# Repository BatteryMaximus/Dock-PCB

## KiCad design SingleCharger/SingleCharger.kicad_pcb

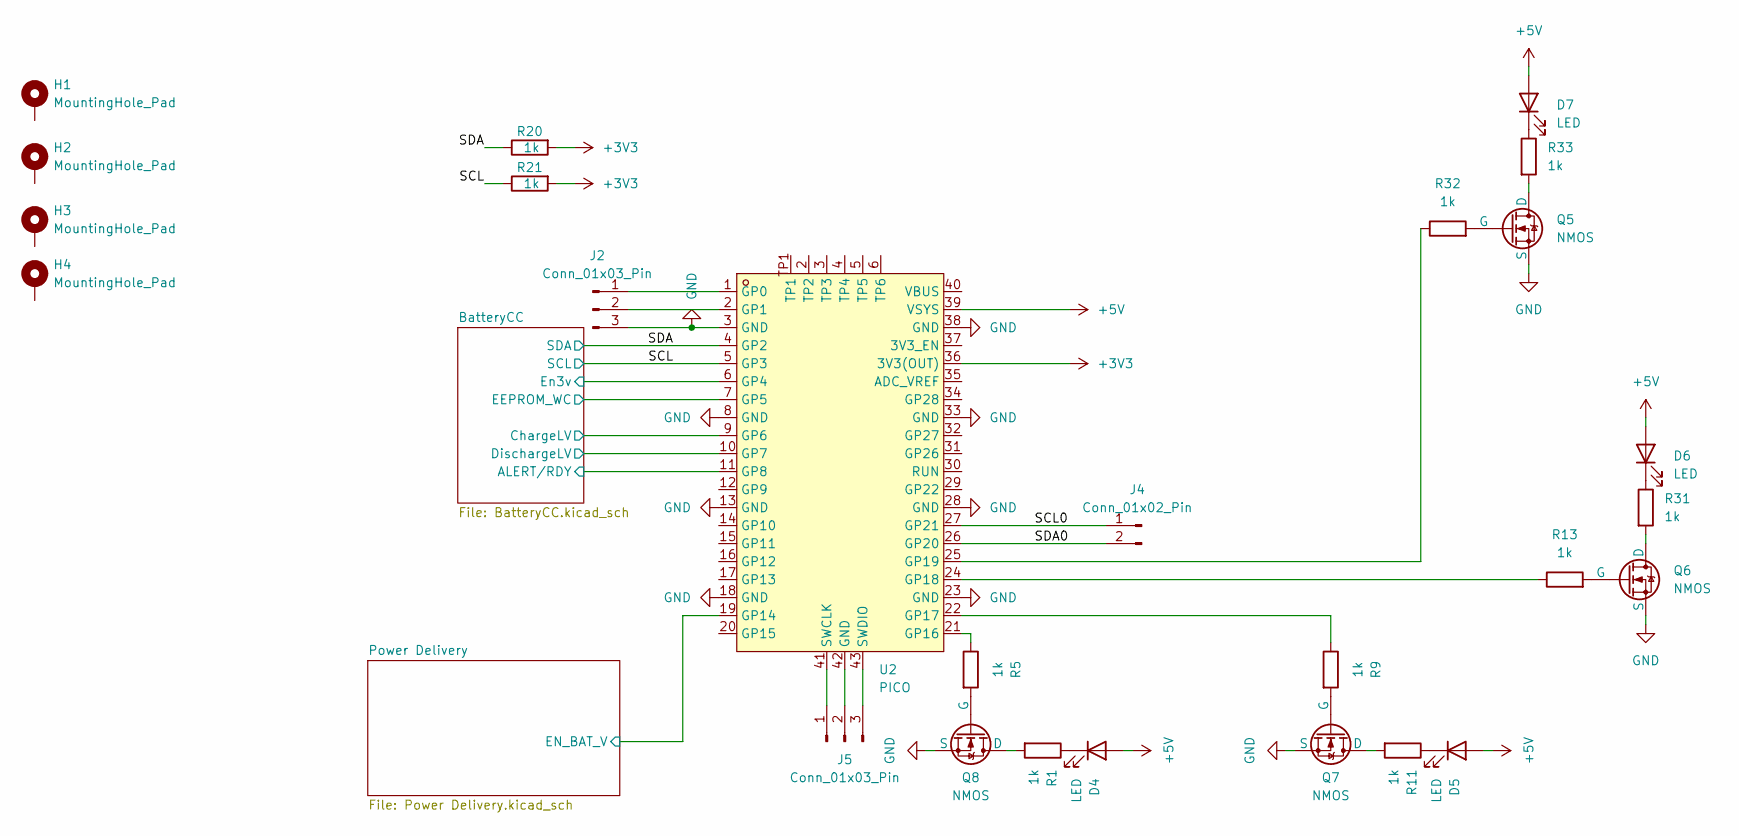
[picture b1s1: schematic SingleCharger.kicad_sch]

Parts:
D4, D5, D6, D7: LED; LED_1206_3216Metric
H1, H2, H3, H4: MountingHole_Pad; MountingHole_3.2mm_M3_DIN965_Pad_TopBottom
J2, J5: Conn_01x03_Pin; PinHeader_1x03_P2.54mm_Horizontal
J4: Conn_01x02_Pin; PinHeader_1x02_P2.54mm_Horizontal
Q5, Q6, Q7, Q8: NMOS; SOT-23
R1, R5, R9, R11, R13, R20, R21, R31, R32, R33: 1k; R_1206_3216Metric
U2: PICO; RaspberryPi_Pico_SMD; LCSC Part C7203002

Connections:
+3V3: R20.2, R21.2, U2.36 (3V3(OUT)); also elsewhere on the board
+5V: D4.2 (A), D5.2 (A), D6.2 (A), D7.2 (A), U2.39 (VSYS); also elsewhere on the board
/BatteryCC/ALERT/RDY: U2.11 (GP8); also elsewhere on the board
/BatteryCC/Battery/EEPROM_WC: U2.7 (GP5); also elsewhere on the board
/BatteryCC/ChargeLV: U2.9 (GP6); also elsewhere on the board
/DischargeLV: U2.10 (GP7)
/En3v: U2.6 (GP4)
/Power Delivery/EN_BAT_V: U2.19 (GP14); also elsewhere on the board
/SCL: R21.1, U2.5 (GP3); also elsewhere on the board
/SCL0: J4.1, U2.27 (GP21)
/SDA: R20.1, U2.4 (GP2); also elsewhere on the board
/SDA0: J4.2, U2.26 (GP20)
GND: J2.3, Q5.2 (S), Q6.2 (S), Q7.2 (S), Q8.2 (S), U2.3 (GND), U2.8 (GND), U2.13 (GND), U2.18 (GND), U2.23 (GND), U2.28 (GND), U2.33 (GND), U2.38 (GND); also elsewhere on the board
unnamed: D4.1 (K), R1.1
unnamed: D5.1 (K), R11.1
unnamed: D6.1 (K), R31.1
unnamed: D7.1 (K), R33.1
unnamed: J2.1, U2.1 (GP0)
unnamed: J2.2, U2.2 (GP1)
unnamed: J5.1, U2.41 (SWCLK)
unnamed: J5.2, U2.42 (GND)
unnamed: J5.3, U2.43 (SWDIO)
unnamed: Q5.3 (D), R33.2
unnamed: Q5.1 (G), R32.2
unnamed: Q6.3 (D), R31.2
unnamed: Q6.1 (G), R13.2
unnamed: Q7.3 (D), R11.2
unnamed: Q7.1 (G), R9.2
unnamed: Q8.3 (D), R1.2
unnamed: Q8.1 (G), R5.2
unnamed: R5.1, U2.21 (GP16)
unnamed: R9.1, U2.22 (GP17)
unnamed: R13.1, U2.24 (GP18)
unnamed: R32.1, U2.25 (GP19)

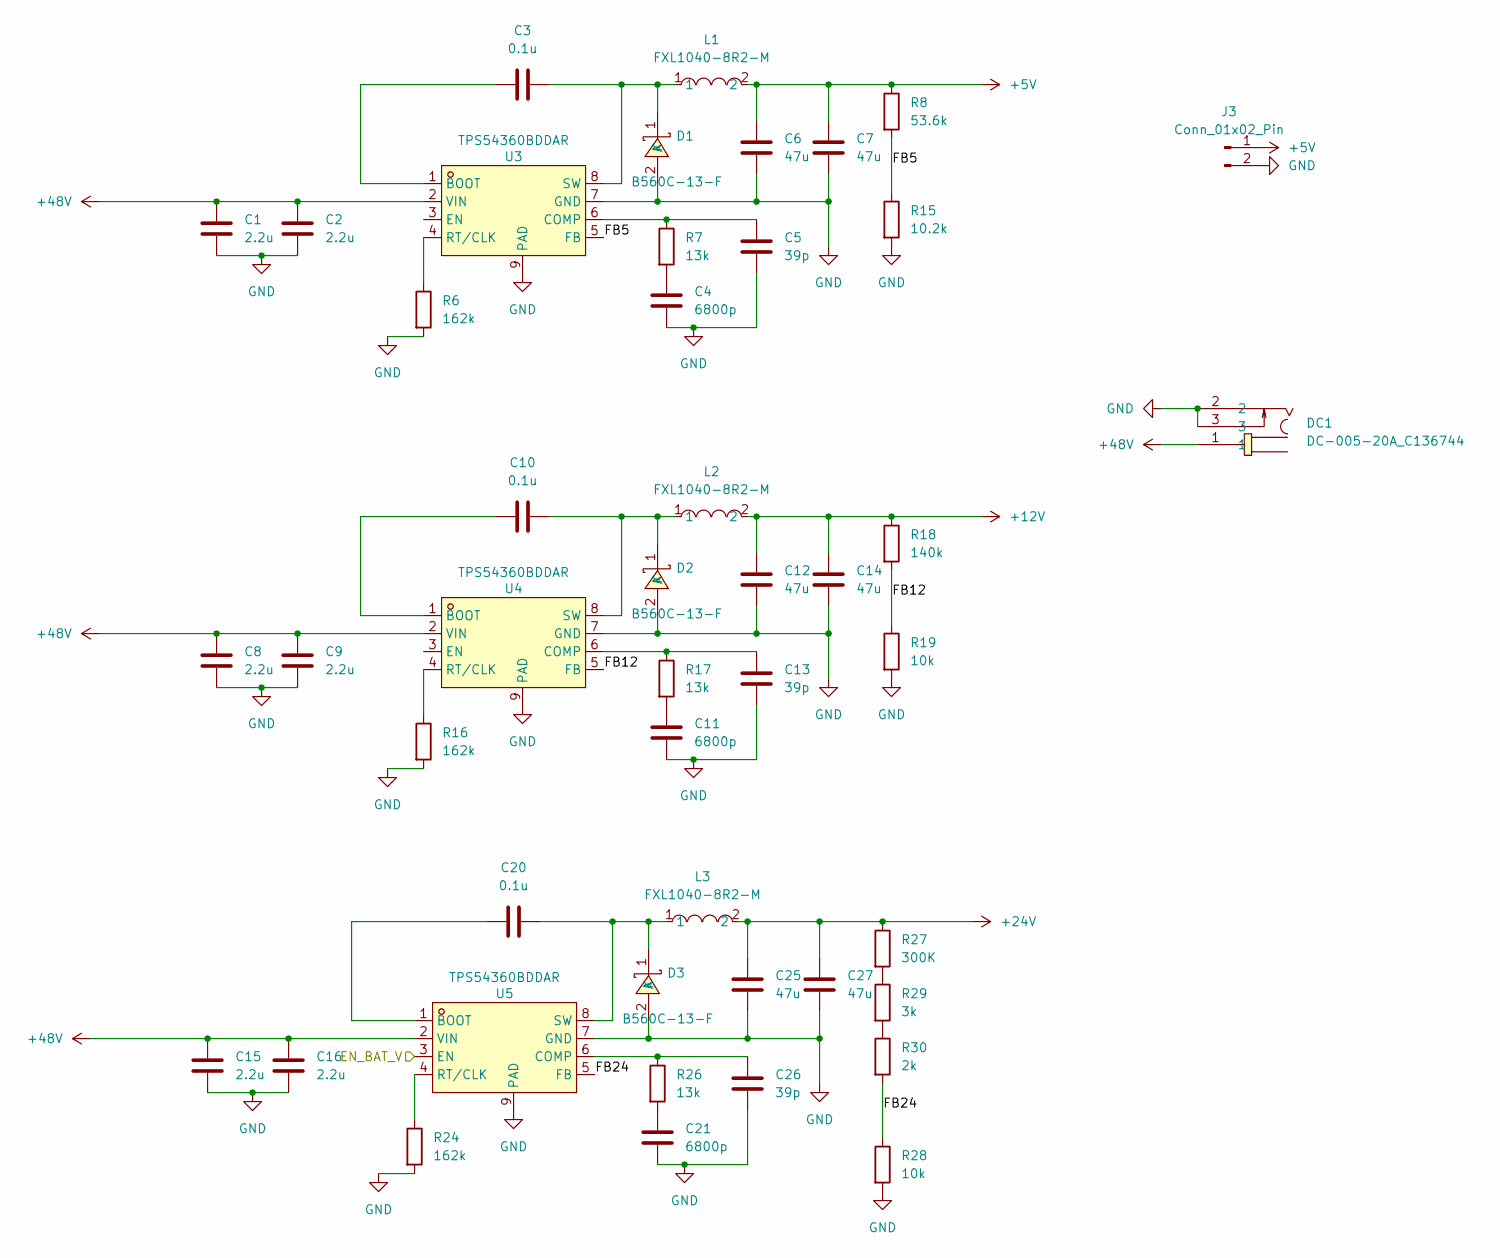
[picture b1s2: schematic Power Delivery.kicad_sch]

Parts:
C1, C2, C8, C9, C15, C16: 2.2u; C_1206_3216Metric; LCSC Part C170101
C3, C10, C20: 0.1u; C_1206_3216Metric; LCSC Part C56392
C4, C11, C21: 6800p; C_1206_3216Metric; LCSC Part C2760541
C5, C13, C26: 39p; C_1206_3216Metric; LCSC Part C5186878
C6, C7, C12, C14, C25, C27: 47u; C_1206_3216Metric; LCSC Part C94034
D1, D2, D3: B560C-13-F; SMC_L7.1-W6.2-LS8.1-RD; LCSC Part C85100
DC1: DC-005-20A_C136744; DC-IN-TH_DC-005-20A; LCSC Part C136744
J3: Conn_01x02_Pin; PinHeader_1x02_P2.54mm_Horizontal
L1, L2, L3: FXL1040-8R2-M; IND-SMD_L11.5-W10.0_FXL1040; LCSC Part C167232
R6, R16, R24: 162k; R_1206_3216Metric_Pad1.30x1.75mm_HandSolder; LCSC Part C22815
R7, R17, R26: 13k; R_1206_3216Metric_Pad1.30x1.75mm_HandSolder; LCSC Part C445658
R8: 53.6k; R_1206_3216Metric_Pad1.30x1.75mm_HandSolder; LCSC Part C21398
R15: 10.2k; R_1206_3216Metric_Pad1.30x1.75mm_HandSolder; LCSC Part C21398
R18: 140k; R_1206_3216Metric_Pad1.30x1.75mm_HandSolder; LCSC Part C21398
R19, R28: 10k; R_1206_3216Metric_Pad1.30x1.75mm_HandSolder; LCSC Part C21398
R27: 300K; R_1206_3216Metric_Pad1.30x1.75mm_HandSolder; LCSC Part C21398
R29: 3k; R_1206_3216Metric_Pad1.30x1.75mm_HandSolder; LCSC Part C21398
R30: 2k; R_1206_3216Metric_Pad1.30x1.75mm_HandSolder; LCSC Part C21398
U3, U4, U5: TPS54360BDDAR; SOIC-8_L5.0-W4.0-P1.27-LS6.0-BL-EP2.0; LCSC Part C524806

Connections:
+5V: C6.1, C7.1, J3.1, L1.2, R8.1; also elsewhere on the board
+12V: C12.1, C14.1, L2.2, R18.1; also elsewhere on the board
+24V: C25.1, C27.1, L3.2, R27.1; also elsewhere on the board
+48V: C1.1, C2.1, C8.1, C9.1, C15.1, C16.1, DC1.1, U3.2 (VIN), U4.2 (VIN), U5.2 (VIN)
/Power Delivery/EN_BAT_V: U5.3 (EN); also elsewhere on the board
/Power Delivery/FB5: R8.2, R15.1, U3.5 (FB)
/Power Delivery/FB12: R18.2, R19.1, U4.5 (FB)
/Power Delivery/FB24: R28.1, R30.2, U5.5 (FB)
GND: C1.2, C2.2, C4.2, C5.2, C6.2, C7.2, C8.2, C9.2, C11.2, C12.2, C13.2, C14.2, C15.2, C16.2, C21.2, C25.2, C26.2, C27.2, D1.2 (A), D2.2 (A), D3.2 (A), DC1.2, DC1.3, J3.2, R6.2, R15.2, R16.2, R19.2, R24.2, R28.2, U3.7 (GND), U3.9 (PAD), U4.7 (GND), U4.9 (PAD), U5.7 (GND), U5.9 (PAD); also elsewhere on the board
unnamed: C4.1, R7.2
unnamed: C11.1, R17.2
unnamed: C21.1, R26.2
unnamed: C3.2, D1.1 (K), L1.1, U3.8 (SW)
unnamed: C10.2, D2.1 (K), L2.1, U4.8 (SW)
unnamed: C20.2, D3.1 (K), L3.1, U5.8 (SW)
unnamed: R27.2, R29.1
unnamed: R29.2, R30.1
unnamed: C3.1, U3.1 (BOOT)
unnamed: C5.1, R7.1, U3.6 (COMP)
unnamed: R6.1, U3.4 (RT/CLK)
unnamed: C10.1, U4.1 (BOOT)
unnamed: C13.1, R17.1, U4.6 (COMP)
unnamed: R16.1, U4.4 (RT/CLK)
unnamed: C20.1, U5.1 (BOOT)
unnamed: C26.1, R26.1, U5.6 (COMP)
unnamed: R24.1, U5.4 (RT/CLK)

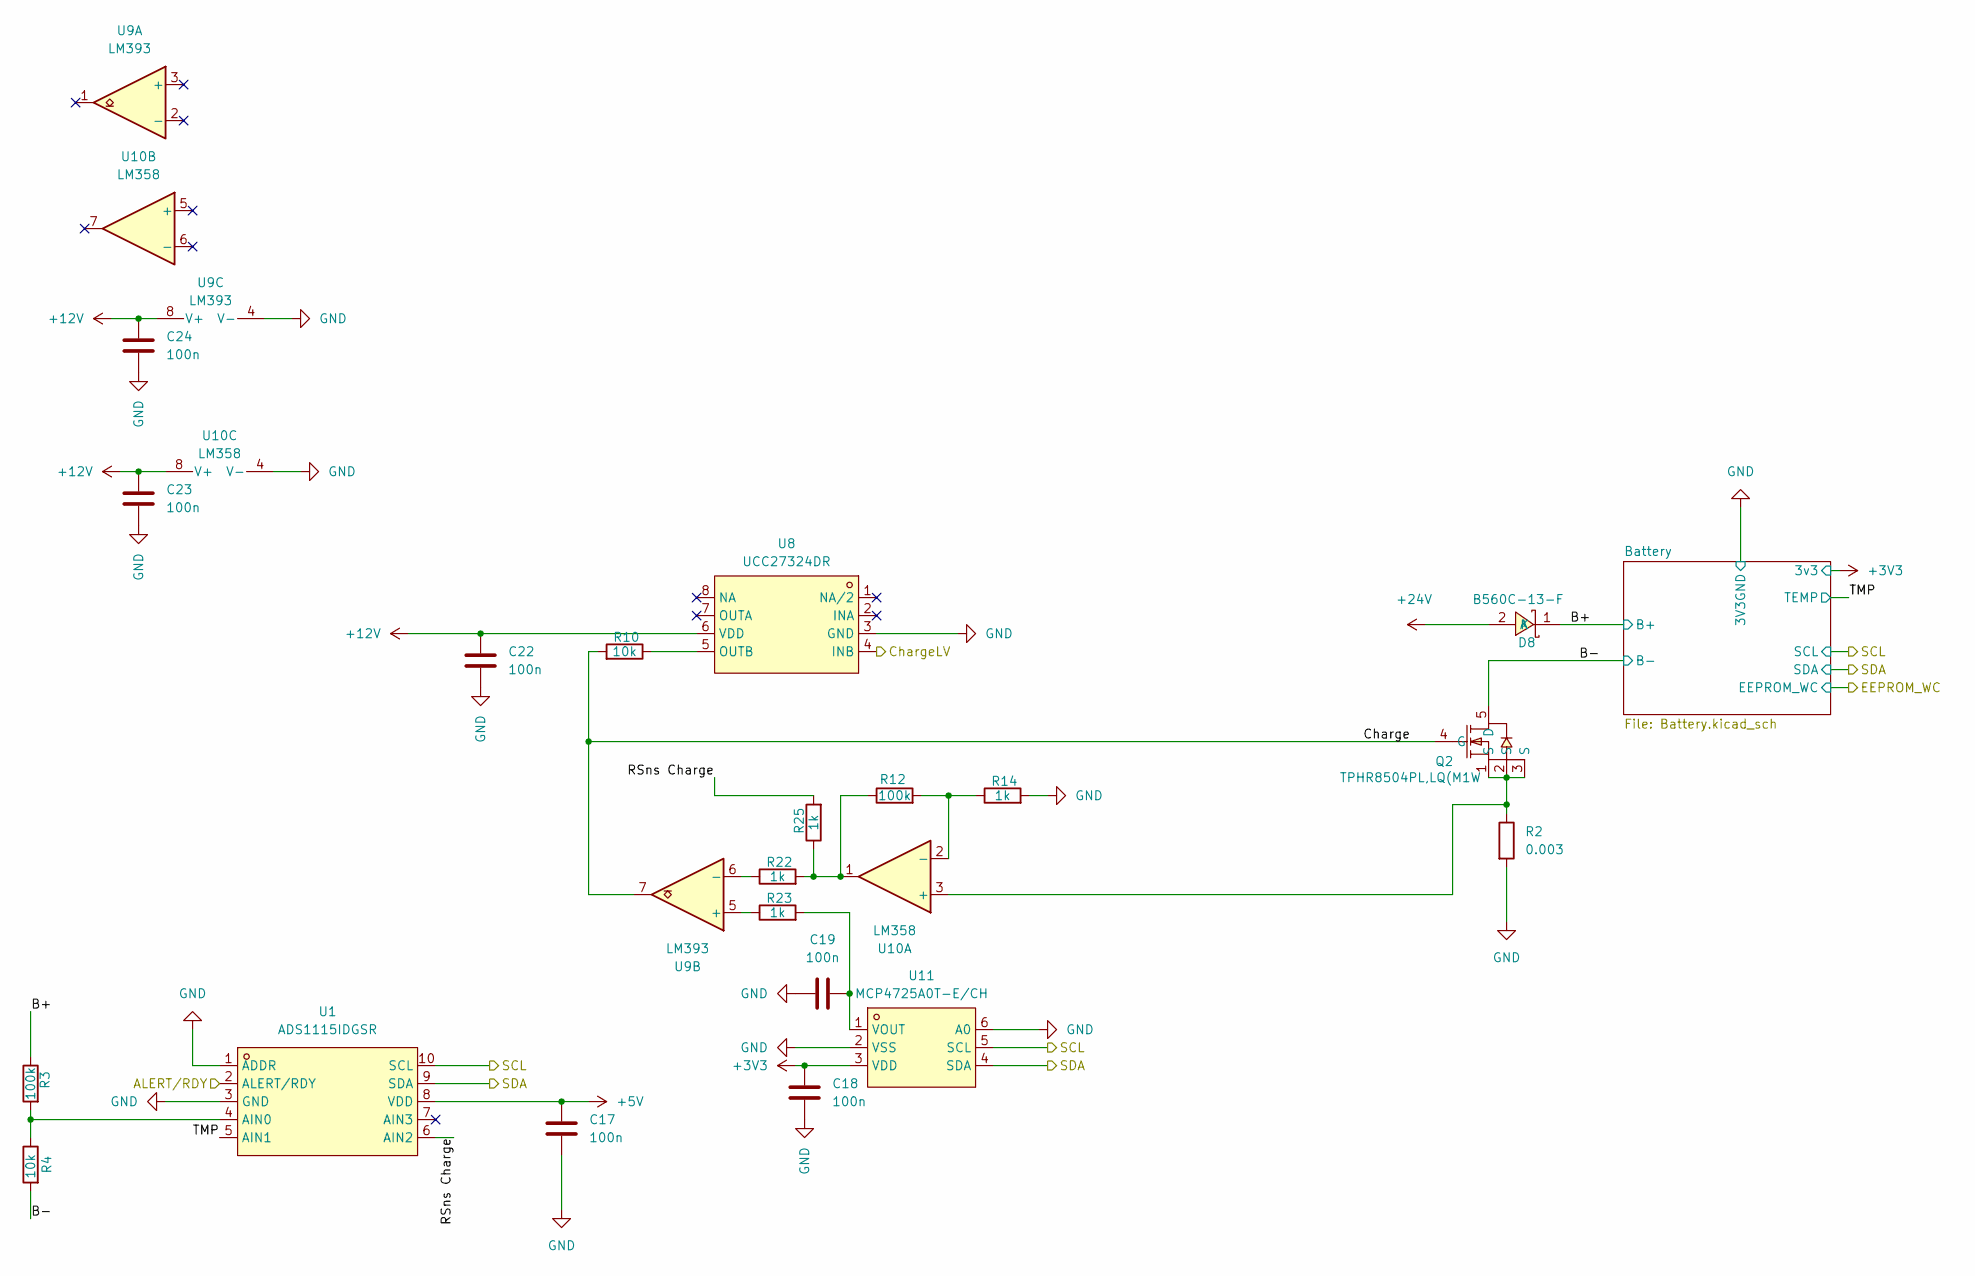
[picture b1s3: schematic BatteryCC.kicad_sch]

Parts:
C17, C18, C19, C22, C23, C24: 100n; R_1206_3216Metric_Pad1.30x1.75mm_HandSolder
D8: B560C-13-F; SMC_L7.1-W6.2-LS8.1-RD; LCSC Part C85100
Q2: TPHR8504PL,LQ(M1W; DFN-5_L4.9-W5.9-P1.27-LS6.2-BL; LCSC Part C22388172
R2: 0.003; R_1206_3216Metric_Pad1.30x1.75mm_HandSolder
R3, R12: 100k; R_1206_3216Metric_Pad1.30x1.75mm_HandSolder
R4, R10: 10k; R_1206_3216Metric_Pad1.30x1.75mm_HandSolder
R14, R22, R23, R25: 1k; R_1206_3216Metric
U1: ADS1115IDGSR; MSOP-10_L3.0-W3.0-P0.50-LS5.0-BL; LCSC Part C37593
U8: UCC27324DR; SOIC-8_L5.0-W4.0-P1.27-LS6.0-BL; LCSC Part C46427
U9: LM393; SOP-8_L4.9-W3.9-P1.27-LS6.0-BL
U10: LM358; SOP-8_L4.9-W3.9-P1.27-LS6.0-BL
U11: MCP4725A0T-E/CH; SOT-23-6_L2.9-W1.6-P0.95-LS2.8-BL; LCSC Part C144198

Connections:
+3V3: C18.1, U11.3 (VDD); also elsewhere on the board
+5V: C17.1, U1.8 (VDD); also elsewhere on the board
+12V: C22.1, C23.1, C24.1, U8.6 (VDD), U9.8 (V+), U10.8 (V+); also elsewhere on the board
+24V: D8.2 (A); also elsewhere on the board
/BatteryCC/ALERT/RDY: U1.2 (ALERT/RDY); also elsewhere on the board
/BatteryCC/B+: D8.1 (K), R3.1; also elsewhere on the board
/BatteryCC/B-: Q2.5 (D), R4.2; also elsewhere on the board
/BatteryCC/Charge: Q2.4 (G), R10.2, U9.7
/BatteryCC/ChargeLV: U8.4 (INB); also elsewhere on the board
/BatteryCC/RSns Charge: R25.2, U1.6 (AIN2)
/BatteryCC/TMP: U1.5 (AIN1); also elsewhere on the board
/SCL: U1.10 (SCL), U11.5 (SCL); also elsewhere on the board
/SDA: U1.9 (SDA), U11.4 (SDA); also elsewhere on the board
GND: C17.2, C18.2, C19.1, C22.2, C23.2, C24.2, R2.2, R14.2, U1.1 (ADDR), U1.3 (GND), U8.3 (GND), U9.4 (V-), U10.4 (V-), U11.2 (VSS), U11.6 (A0); also elsewhere on the board
unnamed: R12.1, R22.2, R25.1, U10.1
unnamed: R3.2, R4.1, U1.4 (AIN0)
unnamed: R10.1, U8.5 (OUTB)
unnamed: R23.1, U9.5 (+)
unnamed: R22.1, U9.6 (-)
unnamed: Q2.1 (S), Q2.2 (S), Q2.3 (S), R2.1, U10.3 (+)
unnamed: R12.2, R14.1, U10.2 (-)
unnamed: C19.2, R23.2, U11.1 (VOUT)

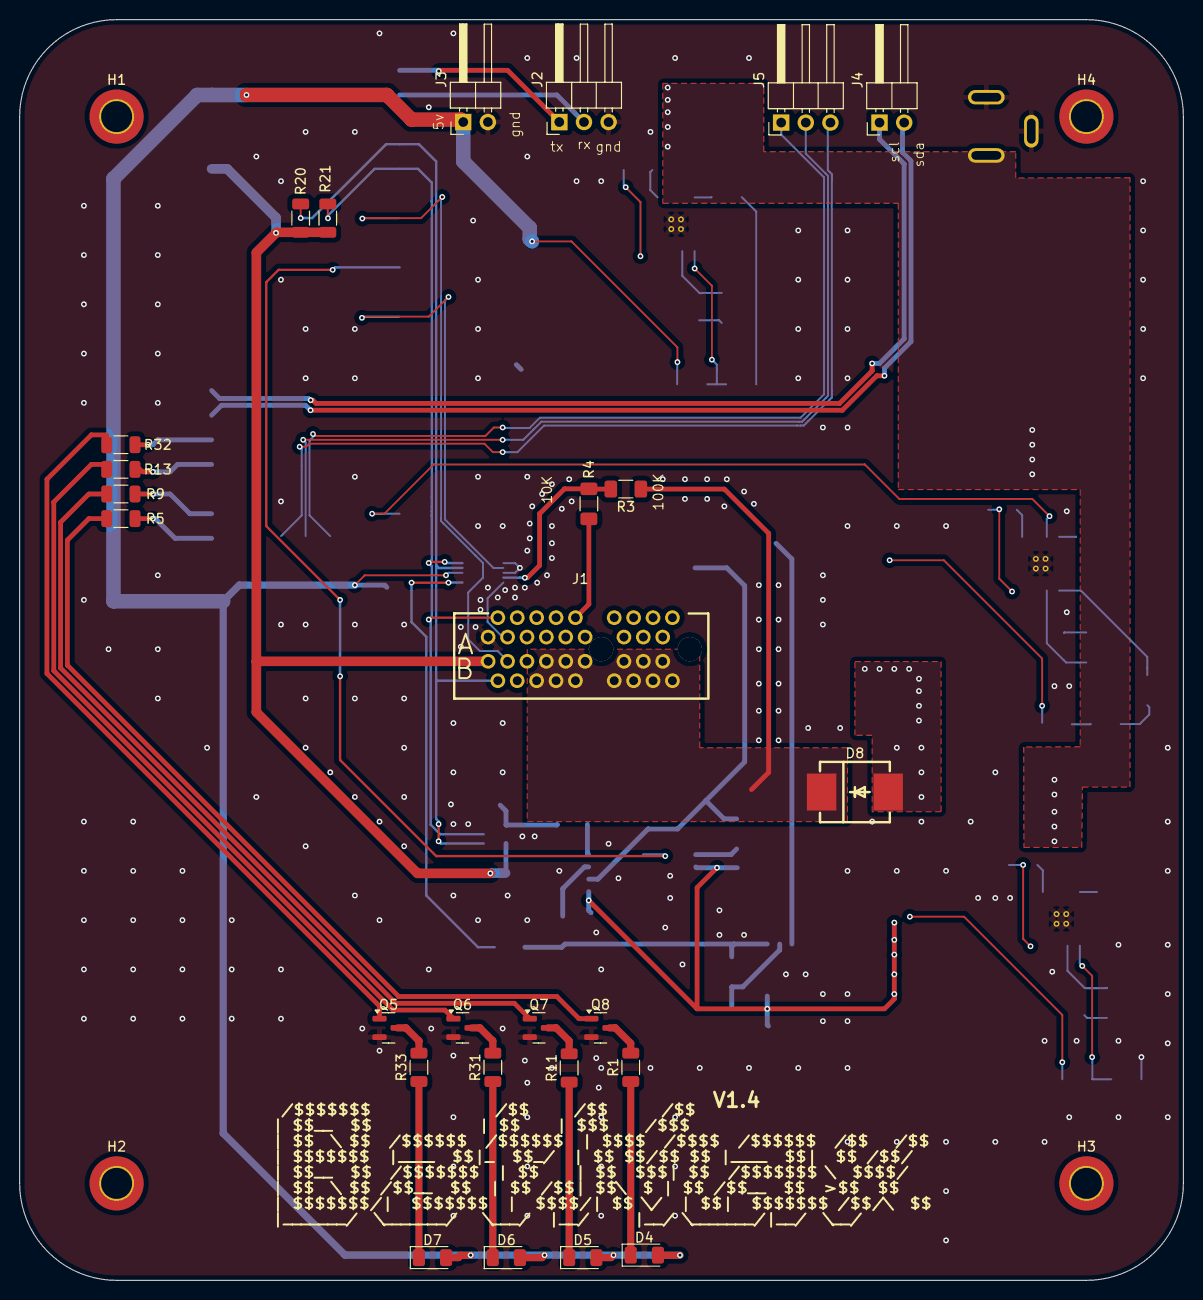
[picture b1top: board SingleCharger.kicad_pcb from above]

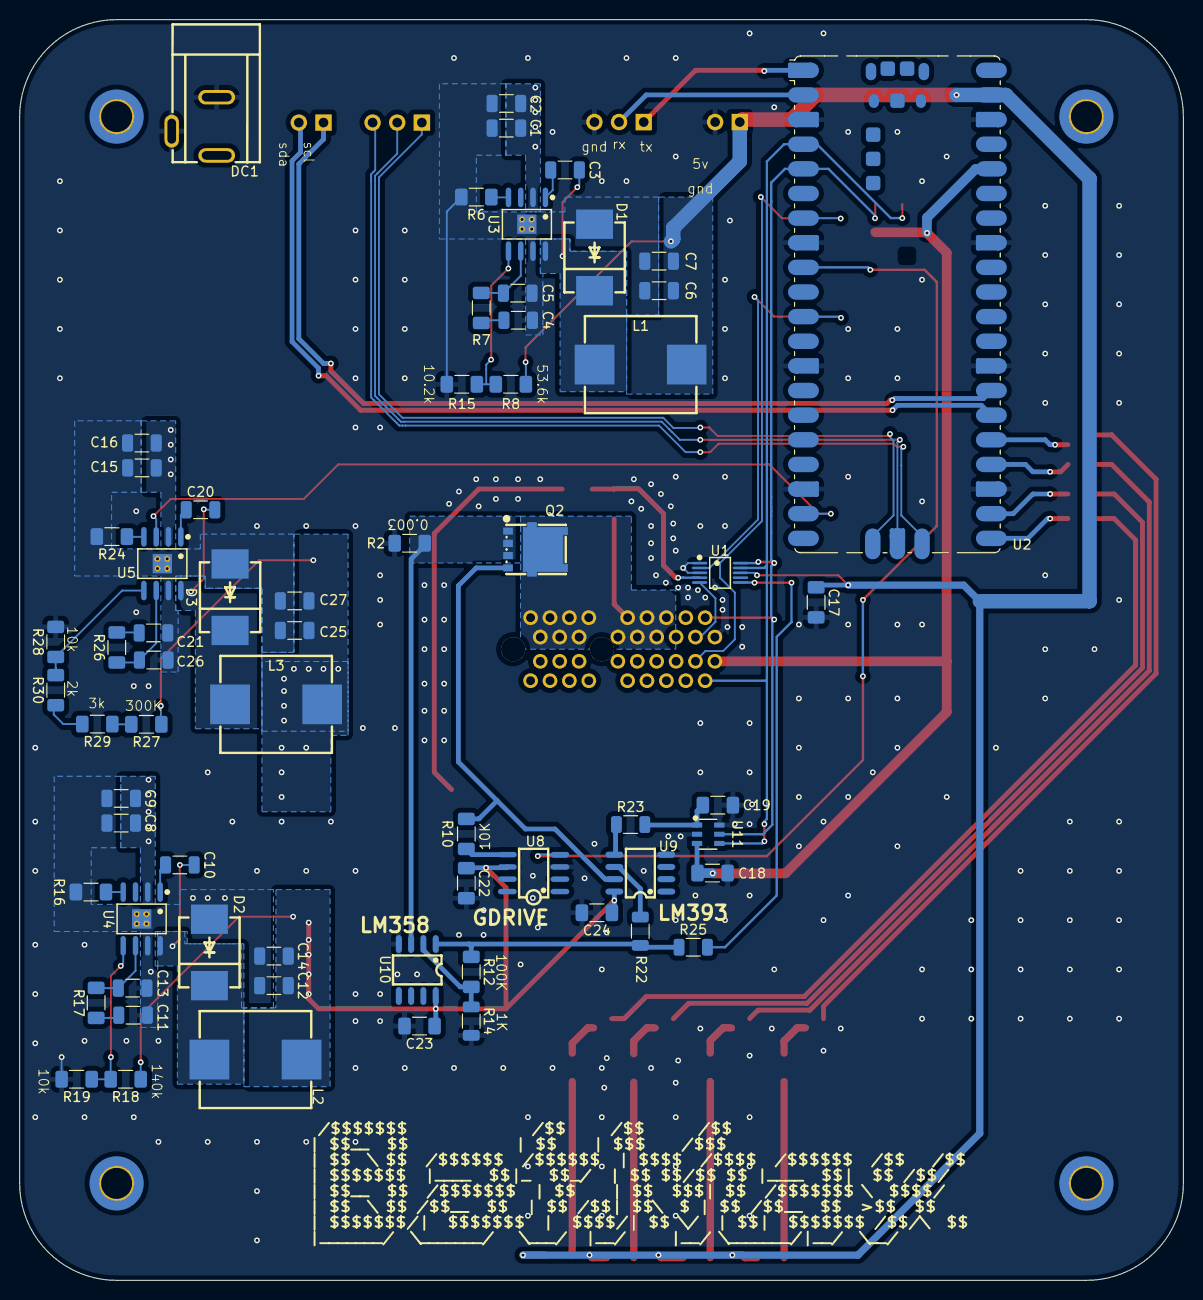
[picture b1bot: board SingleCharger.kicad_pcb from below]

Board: 4 copper layers, 120.0 x 130.0 mm, 95 parts (65 on the bottom side), 68 nets.

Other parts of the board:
J1: Bus_PCI_Express_x1; CONN-TH_36P-P1.00-V_3183-XXXXXPXT

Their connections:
+3V3: J1.B1; also elsewhere on the board
/BatteryCC/B+: J1.B6, J1.B7, J1.B8, J1.B9, J1.B10, J1.B11, J1.B12, J1.B13, J1.B14, J1.B15, J1.B16, J1.B17, J1.B18; also elsewhere on the board
/BatteryCC/B-: J1.A6, J1.A7, J1.A8, J1.A9, J1.A10, J1.A11, J1.A12, J1.A13, J1.A14, J1.A15, J1.A16, J1.A17, J1.A18; also elsewhere on the board
/BatteryCC/Battery/EEPROM_WC: J1.B3; also elsewhere on the board
/BatteryCC/TMP: J1.A3; also elsewhere on the board
/SCL: J1.A2; also elsewhere on the board
/SDA: J1.B2; also elsewhere on the board
GND: J1.A1; also elsewhere on the board

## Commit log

2025-03-31 First push.
2025-04-01 Started adding LEDS
2025-04-01 Added LEDS.
2025-04-01 Working on fixing PICO.
2025-04-01 Finished with layout changes.
2025-04-01 Updated Silkscreen
2025-04-10 Fixed some issues for hopeful stability in analog measuremnets.
2025-04-10 Fixed silkscreen.
